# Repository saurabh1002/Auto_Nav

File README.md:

[Youtube video of 2D mapping in CoE, VJTI](https://youtu.be/3e1LqkSlBaA)

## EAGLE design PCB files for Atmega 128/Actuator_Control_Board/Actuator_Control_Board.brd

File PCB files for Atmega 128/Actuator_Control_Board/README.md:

This PCB splits the motor control signals from the microcontroller to each individual motor driver. It also provides an electrical braking circuit for the motors based on 5 Volt relays.

It also divides the incoming power from the batteries to each actuator.

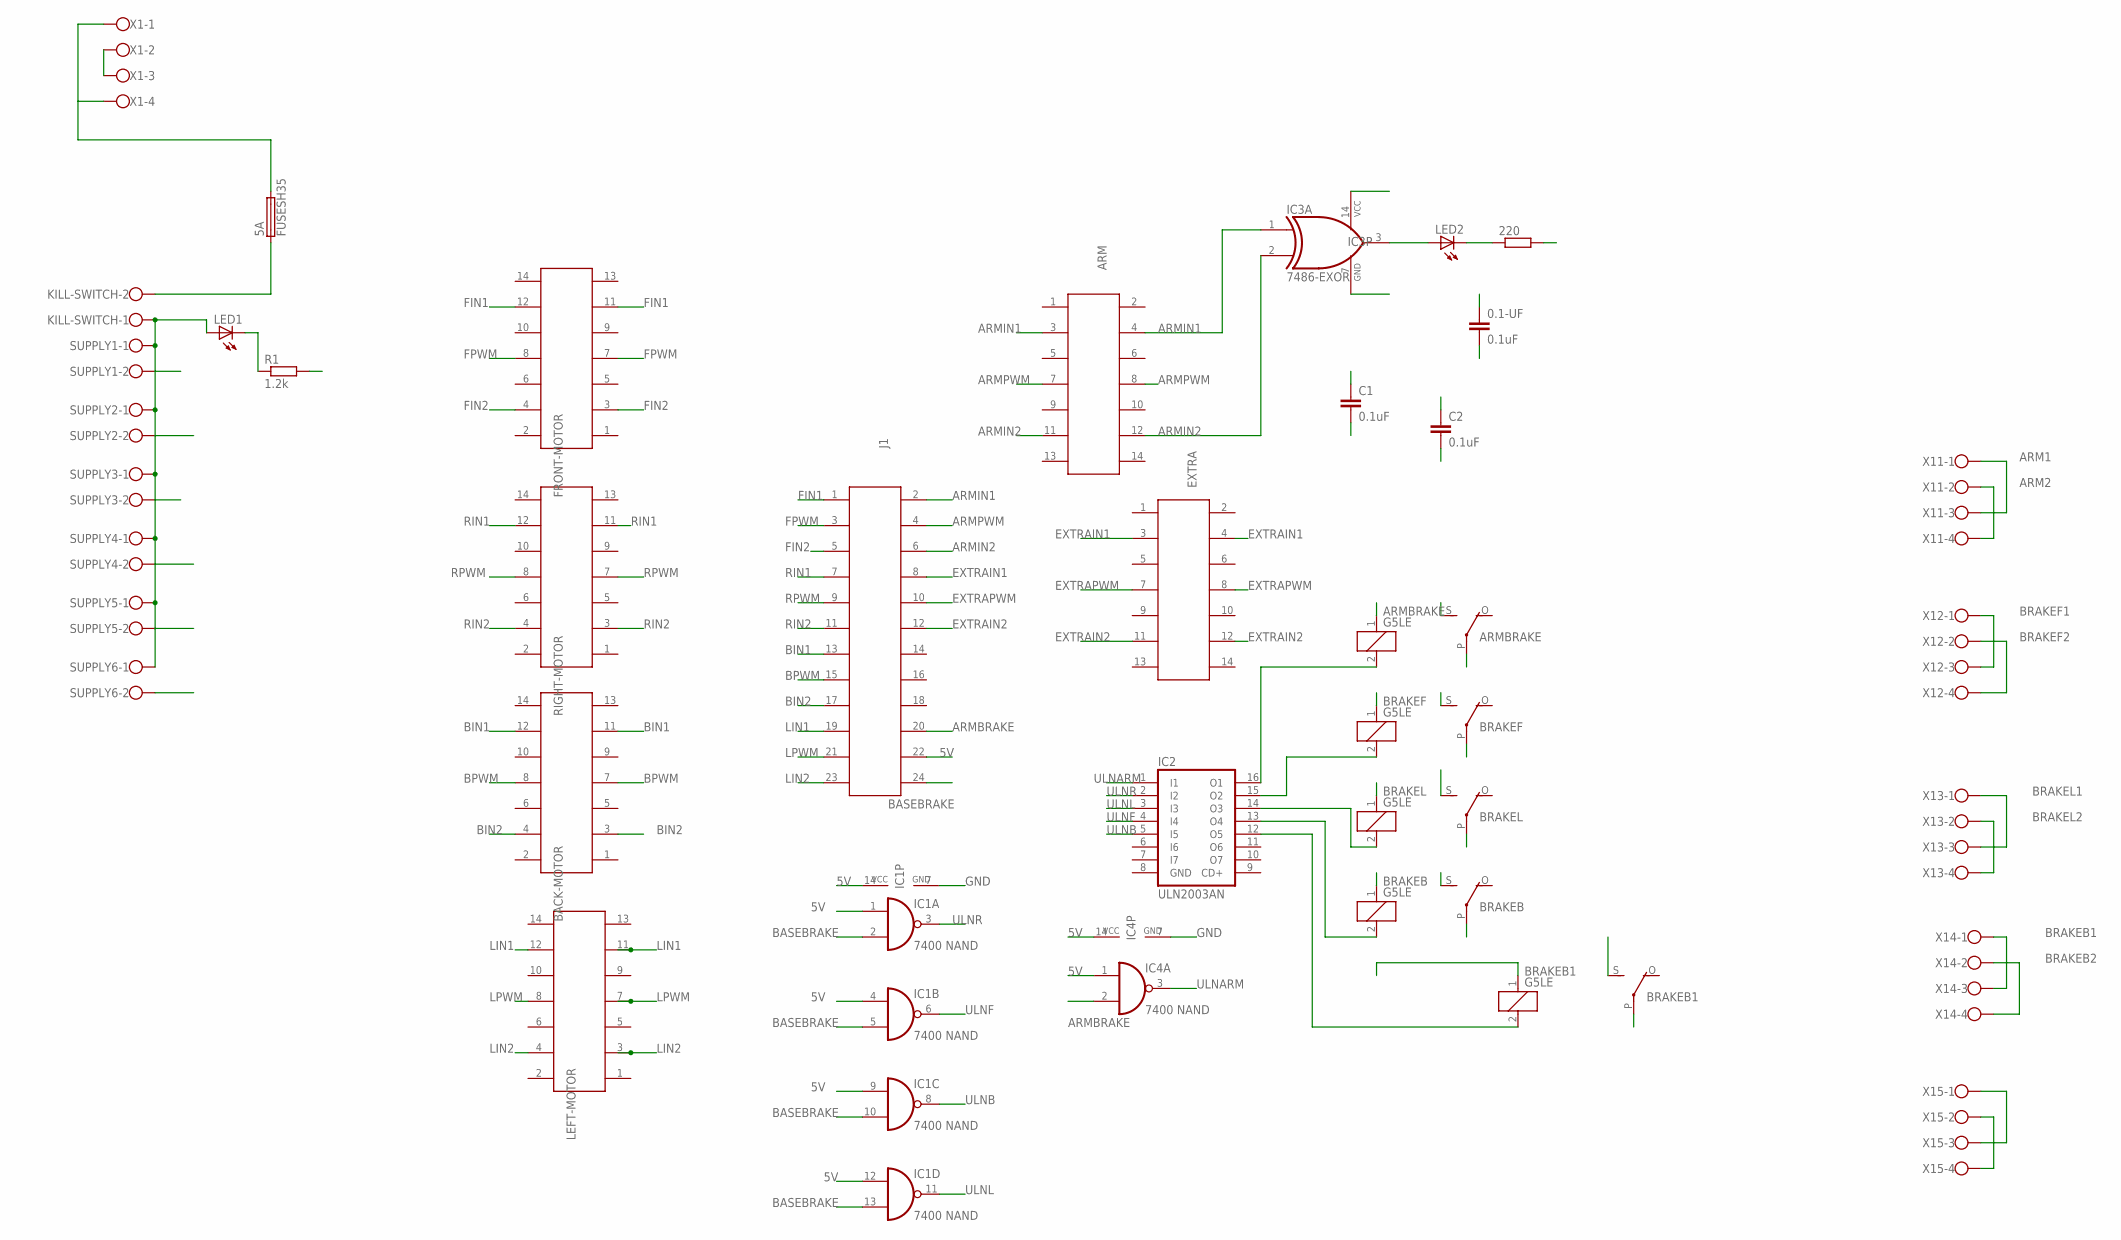
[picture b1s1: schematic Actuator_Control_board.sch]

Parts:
0.1-UF: 0.1uF; C5B2.5
5A: FUSESH35; SH25
220: R-EU_0207/10; 0207/10
ARM: 61201421621
ARMBRAKE: G5LE
BACK-MOTOR: 61201421621
BRAKEB, BRAKEB1: G5LE
BRAKEF: G5LE
BRAKEL: G5LE
C1, C2: 0.1uF; C5B2.5
EXTRA: 61201421621
FRONT-MOTOR: 61201421621
IC1, IC4: 7400 NAND; DIL14
IC2: ULN2003AN; DIL16
IC3: 7486-EXOR; DIL14
J1: 61202421621
KILL-SWITCH: W237-102
LED1, LED2: LED5MM
LEFT-MOTOR: 61201421621
R1: 1.2k; 0617/17
RIGHT-MOTOR: 61201421621
SUPPLY1, SUPPLY2, SUPPLY3, SUPPLY4, SUPPLY5, SUPPLY6: W237-102
X1, X11, X12, X13, X14, X15: W237-4

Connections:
5V: 0.1-UF.1, ARMBRAKE.1, BRAKEB.1, BRAKEB1.1, BRAKEF.1, BRAKEL.1, C1.1, C2.1, IC1.1 (I0), IC1.4 (I0), IC1.9 (I0), IC1.12 (I0), IC1.14 (VCC), IC3.14 (VCC), IC4.1 (I0), IC4.14 (VCC), J1.22
ARM1: ARMBRAKE.P, X11.1, X11.3
ARM2: ARMBRAKE.S, X11.2, X11.4
ARMBRAKE: IC4.2 (I1), J1.20
ARMIN1: ARM.3, ARM.4, IC3.1 (I0), J1.2
ARMIN2: ARM.11, ARM.12, IC3.2 (I1), J1.6
ARMPWM: ARM.7, ARM.8, J1.4
BASEBRAKE: IC1.2 (I1), IC1.5 (I1), IC1.10 (I1), IC1.13 (I1), J1.24
BIN1: BACK-MOTOR.11, BACK-MOTOR.12, J1.13
BIN2: BACK-MOTOR.3, BACK-MOTOR.4, J1.17
BPWM: BACK-MOTOR.7, BACK-MOTOR.8, J1.15
BRAKEB1: BRAKEB.P, X14.1, X14.3
BRAKEB2: BRAKEB.S, X14.2, X14.4
BRAKEF1: BRAKEF.P, X12.1, X12.3
BRAKEF2: BRAKEF.S, X12.2, X12.4
BRAKEL1: BRAKEL.P, X13.1, X13.3
BRAKEL2: BRAKEL.S, X13.2, X13.4
BRAKER1: BRAKEB1.P, X15.1, X15.3
BRAKER2: BRAKEB1.S, X15.2, X15.4
EXTRAIN1: EXTRA.3, EXTRA.4, J1.8
EXTRAIN2: EXTRA.11, EXTRA.12, J1.12
EXTRAPWM: EXTRA.7, EXTRA.8, J1.10
FIN1: FRONT-MOTOR.11, FRONT-MOTOR.12, J1.1
FIN2: FRONT-MOTOR.3, FRONT-MOTOR.4, J1.5
FPWM: FRONT-MOTOR.7, FRONT-MOTOR.8, J1.3
GND: 0.1-UF.2, 220.2, C1.2, C2.2, IC1.7 (GND), IC2.8 (GND), IC3.7 (GND), IC4.7 (GND), R1.2, SUPPLY1.2, SUPPLY2.2, SUPPLY3.2, SUPPLY4.2, SUPPLY5.2, SUPPLY6.2, X1.2, X1.3
LIN1: J1.19, LEFT-MOTOR.11, LEFT-MOTOR.12
LIN2: J1.23, LEFT-MOTOR.3, LEFT-MOTOR.4
LPWM: J1.21, LEFT-MOTOR.7, LEFT-MOTOR.8
unnamed: ARMBRAKE.2, IC2.16 (O1)
unnamed: BRAKEF.2, IC2.15 (O2)
unnamed: BRAKEL.2, IC2.14 (O3)
unnamed: BRAKEB.2, IC2.13 (O4)
unnamed: BRAKEB1.2, IC2.12 (O5)
unnamed: 5A.2, X1.1, X1.4
unnamed: 5A.1, KILL-SWITCH.2
unnamed: KILL-SWITCH.1, LED1.A, SUPPLY1.1, SUPPLY2.1, SUPPLY3.1, SUPPLY4.1, SUPPLY5.1, SUPPLY6.1
unnamed: LED1.K (C), R1.1
unnamed: IC3.3 (O), LED2.A
unnamed: 220.1, LED2.K (C)
RIN1: J1.7, RIGHT-MOTOR.11, RIGHT-MOTOR.12
RIN2: J1.11, RIGHT-MOTOR.3, RIGHT-MOTOR.4
RPWM: J1.9, RIGHT-MOTOR.7, RIGHT-MOTOR.8
ULNARM: IC2.1 (I1), IC4.3 (O)
ULNB: IC1.8 (O), IC2.5 (I5)
ULNF: IC1.6 (O), IC2.4 (I4)
ULNL: IC1.11 (O), IC2.3 (I3)
ULNR: IC1.3 (O), IC2.2 (I2)

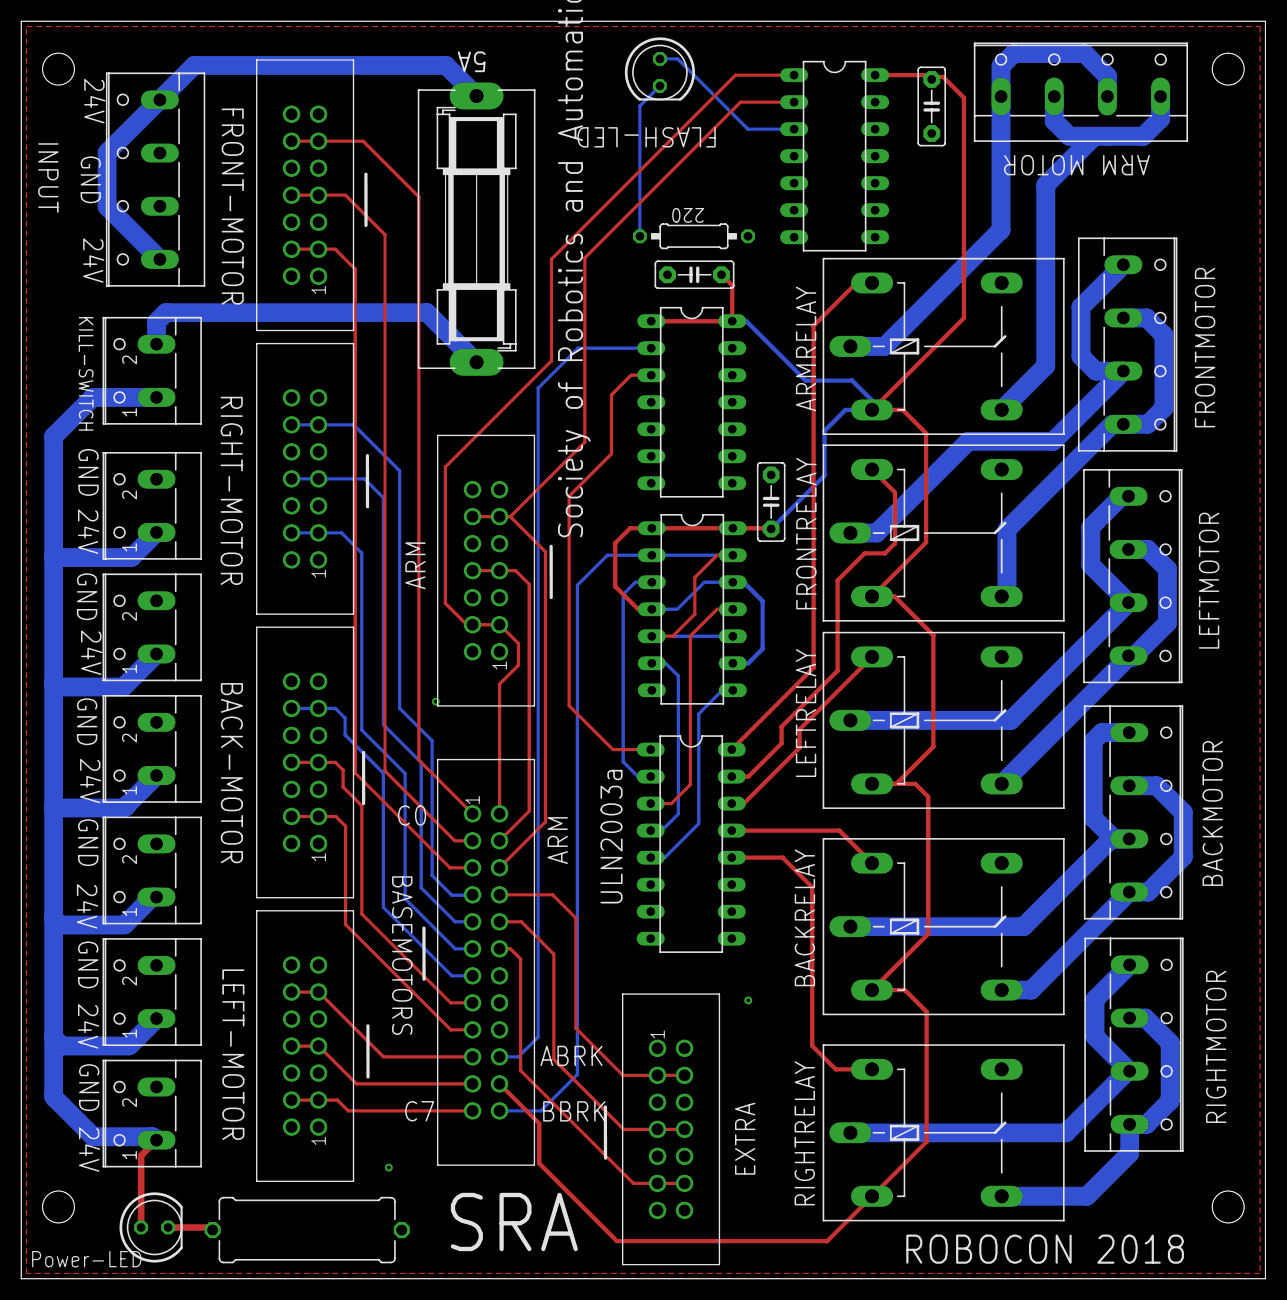
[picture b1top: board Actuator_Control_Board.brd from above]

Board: 2 copper layers, 117.0 x 118.2 mm, 37 parts (0 on the bottom side), 48 nets.

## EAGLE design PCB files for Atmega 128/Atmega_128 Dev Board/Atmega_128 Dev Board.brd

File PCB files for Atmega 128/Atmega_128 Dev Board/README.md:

This is the main PCB for the Atmega 128 based development board. The Atmega 128 breakout board must be inserted into this PCB and a 12x2 FRC cable must be connected to the Actuator control board for transmitting IO signals to the motor drivers.

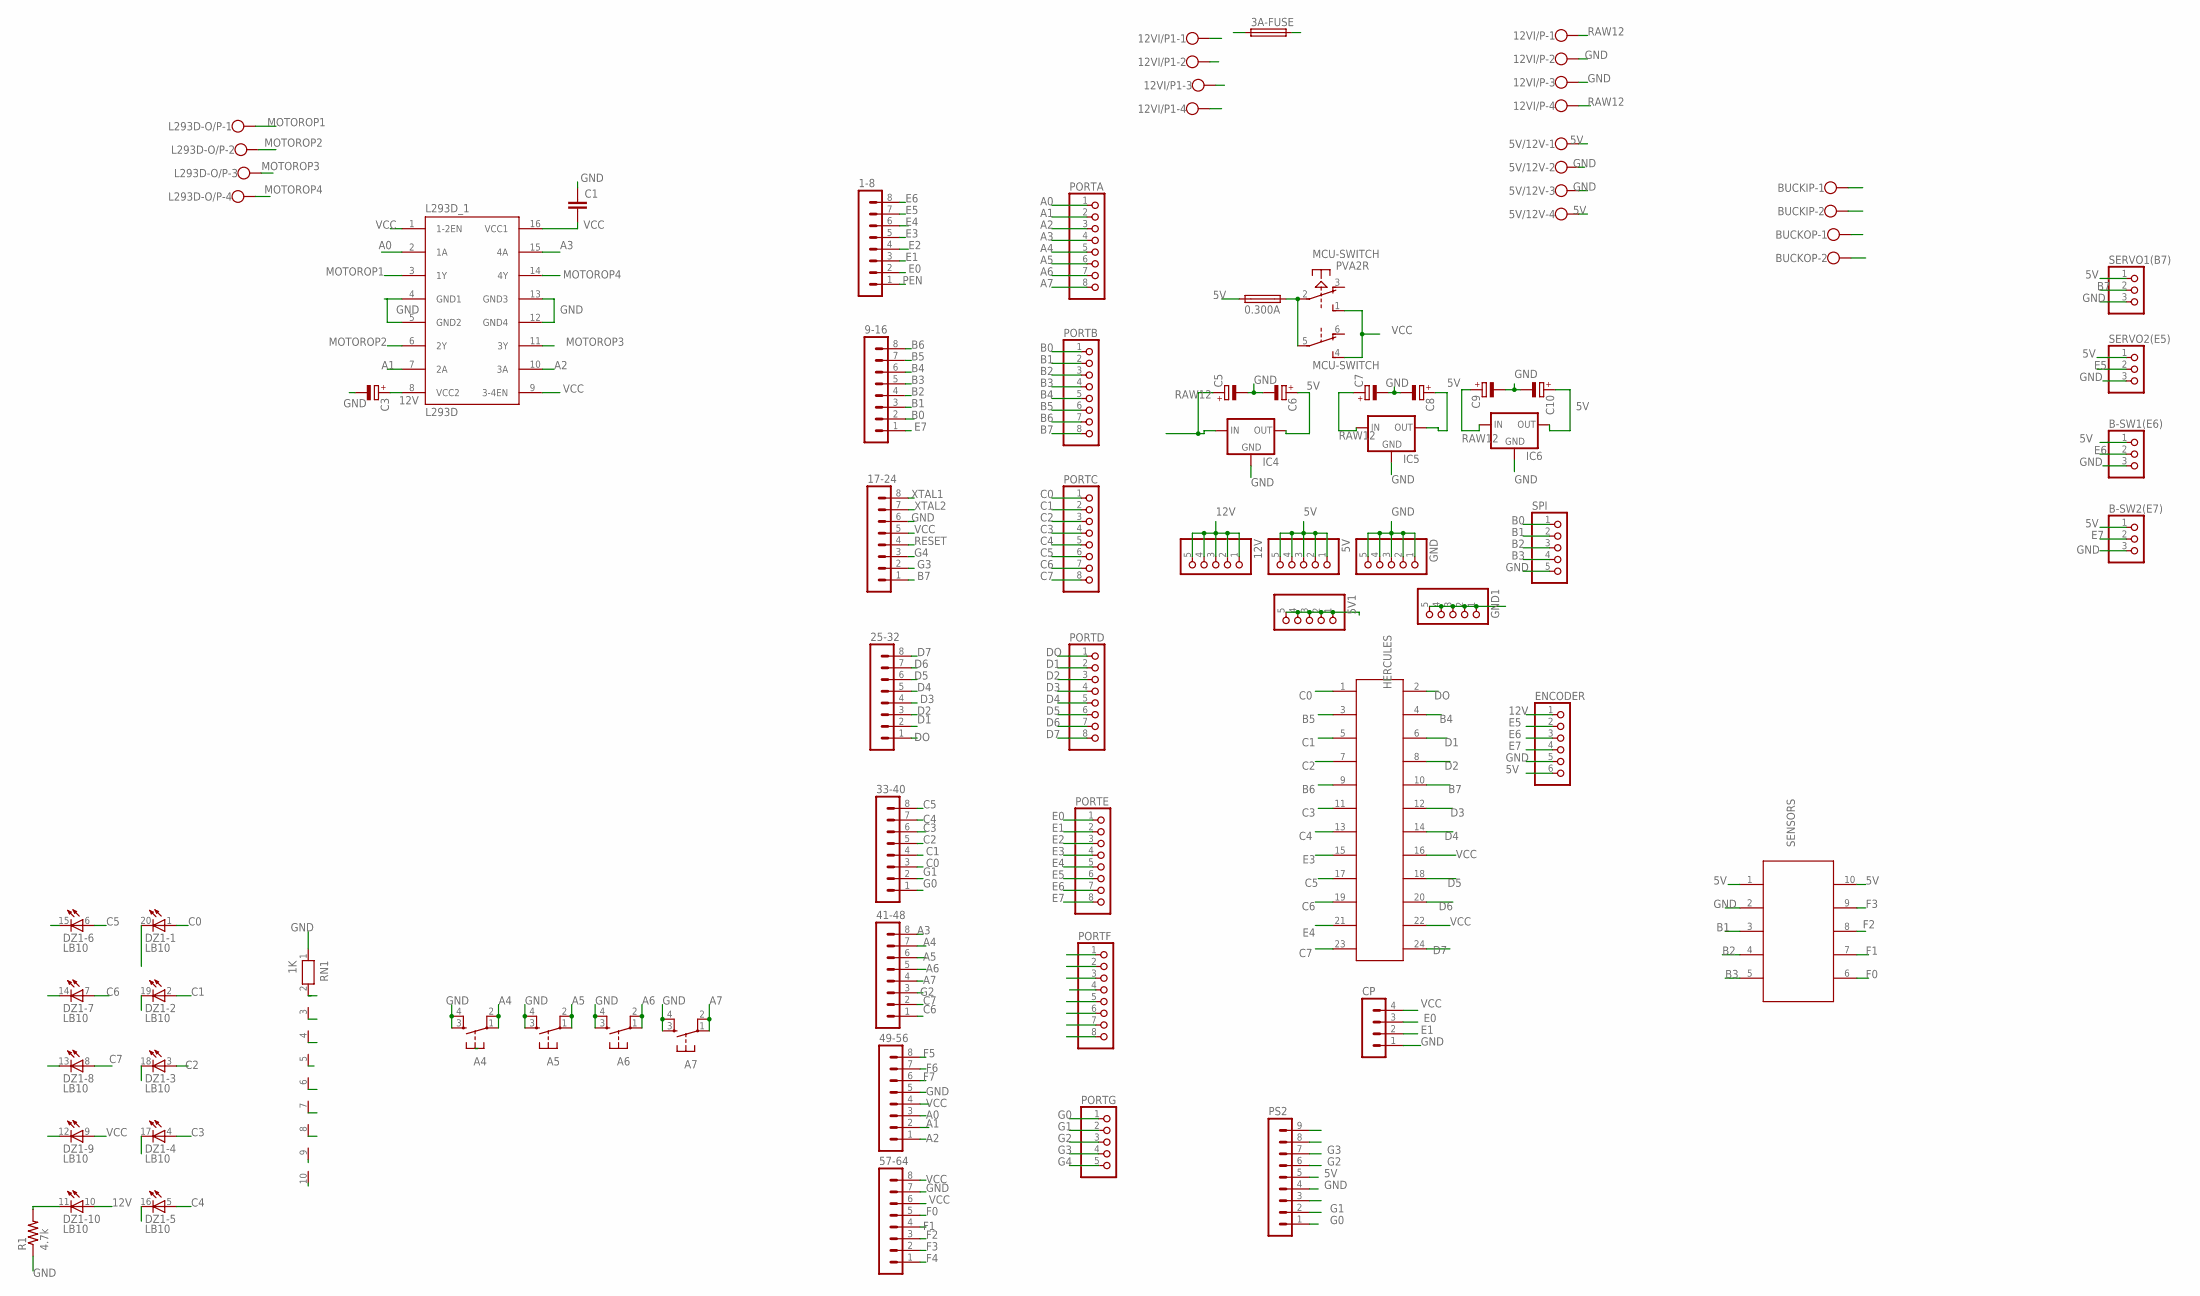
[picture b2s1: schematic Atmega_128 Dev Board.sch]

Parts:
0.300A, 3A-FUSE: SH25
1-8, 9-16, 17-24, 25-32, 33-40, 41-48, 49-56, 57-64: MA08-1
5V, 5V1, 12V: PINHD-1X5; 1X05
5V/12V, 12VI/P, 12VI/P1: W237-4
A4, A5, A6, A7: DTS-6
B-SW1(E6), B-SW2(E7): PINHD-1X3; 1X03
BUCKIP: W237-102
BUCKOP: W237-102
C1: C5/2.5; C5B2.5
C3, C5, C6, C7, C8, C9, C10: CPOL-EUE2.5-5; E2,5-5
CP: MA04-1
DZ1: LB10
ENCODER: PINHD-1X6; 1X06
GND, GND1: PINHD-1X5; 1X05
HERCULES: 61202421621
IC4, IC5, IC6: 78XXS
L293D-O/P: W237-4
L293D_1: L293D; DIL16
MCU-SWITCH: PVA2R
PORTA: PINHD-1X8; 1X08
PORTB: PINHD-1X8; 1X08
PORTC: PINHD-1X8; 1X08
PORTD: PINHD-1X8; 1X08
PORTE: PINHD-1X8; 1X08
PORTF: PINHD-1X8; 1X08
PORTG: PINHD-1X5; 1X05
PS2: MA09-1
R1: 4.7k; 0204/7
RN1: 1K; RN-10
SENSORS: 66101021622
SERVO1(B7), SERVO2(E5): PINHD-1X3; 1X03
SPI: PINHD-1X5; 1X05

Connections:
2: DZ1.12 (C), RN1.2
3: DZ1.13 (C), RN1.3
4: DZ1.14 (C), RN1.4
5: DZ1.15 (C), RN1.5
5V: 0.300A.2, 5V.1, 5V.2, 5V.3, 5V.4, 5V.5, 5V1.1, 5V1.2, 5V1.3, 5V1.4, 5V1.5, 5V/12V.1, 5V/12V.4, B-SW1(E6).1, B-SW2(E7).1, BUCKOP.2, C6.+, C8.+, C10.+, ENCODER.6, IC4.OUT, IC5.OUT, IC6.OUT, PS2.5, SENSORS.1 (6), SENSORS.10 (1), SERVO1(B7).1, SERVO2(E5).1
5V-F: 0.300A.1, MCU-SWITCH.2, MCU-SWITCH.5
6: DZ1.16 (C), RN1.6
7: DZ1.17 (C), RN1.7
8: DZ1.18 (C), RN1.8
9: DZ1.19 (C), RN1.9
10: DZ1.20 (C), RN1.10
12V: 3A-FUSE.2, 12V.1, 12V.2, 12V.3, 12V.4, 12V.5, C3.+, DZ1.10 (A), ENCODER.1, L293D_1.8 (VCC2)
A0: 49-56.3, L293D_1.2 (1A), PORTA.1
A1: 49-56.2, L293D_1.7 (2A), PORTA.2
A2: 49-56.1, L293D_1.10 (3A), PORTA.3
A3: 41-48.8, L293D_1.15 (4A), PORTA.4
A4: 41-48.7, A4.1, A4.2, PORTA.5
A5: 41-48.6, A5.1, A5.2, PORTA.6
A6: 41-48.5, A6.1, A6.2, PORTA.7
A7: 41-48.4, A7.1, A7.2, PORTA.8
B0: 9-16.2, PORTB.1, SPI.1
B1: 9-16.3, PORTB.2, SENSORS.3 (8), SPI.2
B2: 9-16.4, PORTB.3, SENSORS.4 (9), SPI.3
B3: 9-16.5, PORTB.4, SENSORS.5 (10), SPI.4
B4: 9-16.6, HERCULES.4, PORTB.5
B5: 9-16.7, HERCULES.3, PORTB.6
B6: 9-16.8, HERCULES.9, PORTB.7
B7: 17-24.1, HERCULES.10, PORTB.8, SERVO1(B7).2
C0: 33-40.3, DZ1.1 (A), HERCULES.1, PORTC.1
C1: 33-40.4, DZ1.2 (A), HERCULES.5, PORTC.2
C2: 33-40.5, DZ1.3 (A), HERCULES.7, PORTC.3
C3: 33-40.6, DZ1.4 (A), HERCULES.11, PORTC.4
C4: 33-40.7, DZ1.5 (A), HERCULES.13, PORTC.5
C5: 33-40.8, DZ1.6 (A), HERCULES.17, PORTC.6
C6: 41-48.1, DZ1.7 (A), HERCULES.19, PORTC.7
C7: 41-48.2, DZ1.8 (A), HERCULES.23, PORTC.8
D1: 25-32.2, HERCULES.6, PORTD.2
D2: 25-32.3, HERCULES.8, PORTD.3
D3: 25-32.4, HERCULES.12, PORTD.4
D4: 25-32.5, HERCULES.14, PORTD.5
D5: 25-32.6, HERCULES.18, PORTD.6
D6: 25-32.7, HERCULES.20, PORTD.7
D7: 25-32.8, HERCULES.24, PORTD.8
DO: 25-32.1, HERCULES.2, PORTD.1
E0: 1-8.2, CP.3, PORTE.1
E1: 1-8.3, CP.2, PORTE.2
E2: 1-8.4, PORTE.3
E3: 1-8.5, HERCULES.15, PORTE.4
E4: 1-8.6, HERCULES.21, PORTE.5
E5: 1-8.7, ENCODER.2, PORTE.6, SERVO2(E5).2
E6: 1-8.8, B-SW1(E6).2, ENCODER.3, PORTE.7
E7: 9-16.1, B-SW2(E7).2, ENCODER.4, PORTE.8
F0: 57-64.5, PORTF.1, SENSORS.6 (5)
F1: 57-64.4, PORTF.2, SENSORS.7 (4)
F2: 57-64.3, PORTF.3, SENSORS.8 (3)
F3: 57-64.2, PORTF.4, SENSORS.9 (2)
F4: 57-64.1, PORTF.5
F5: 49-56.8, PORTF.6
F6: 49-56.7, PORTF.7
F7: 49-56.6, PORTF.8
G0: 33-40.1, PORTG.1, PS2.1
G1: 33-40.2, PORTG.2, PS2.2
G2: 41-48.3, PORTG.3, PS2.6
G3: 17-24.2, PORTG.4, PS2.7
G4: 17-24.3, PORTG.5
GND: 5V/12V.2, 5V/12V.3, 12VI/P.2, 12VI/P.3, 12VI/P1.2, 12VI/P1.3, 17-24.6, 49-56.5, 57-64.7, A4.3, A4.4, A5.3, A5.4, A6.3, A6.4, A7.3, A7.4, B-SW1(E6).3, B-SW2(E7).3, BUCKIP.2, BUCKOP.1, C1.1, C3.-, C5.-, C6.-, C7.-, C8.-, C9.-, C10.-, CP.1, ENCODER.5, GND.1, GND.2, GND.3, GND.4, GND.5, GND1.1, GND1.2, GND1.3, GND1.4, GND1.5, IC4.GND, IC5.GND, IC6.GND, L293D_1.4 (GND1), L293D_1.5 (GND2), L293D_1.12 (GND4), L293D_1.13 (GND3), PS2.4, R1.1, RN1.1, SENSORS.2 (7), SERVO1(B7).3, SERVO2(E5).3, SPI.5
MOTOROP1: L293D-O/P.1, L293D_1.3 (1Y)
MOTOROP2: L293D-O/P.2, L293D_1.6 (2Y)
MOTOROP3: L293D-O/P.3, L293D_1.11 (3Y)
MOTOROP4: L293D-O/P.4, L293D_1.14 (4Y)
unnamed: DZ1.11 (C), R1.2
PEN: 1-8.1
RAW12: 3A-FUSE.1, 12VI/P.1, 12VI/P.4, 12VI/P1.1, 12VI/P1.4, BUCKIP.1, C5.+, C7.+, C9.+, IC4.IN, IC5.IN, IC6.IN
RESET: 17-24.4
VCC: 17-24.5, 49-56.4, 57-64.6, 57-64.8, C1.2, CP.4, DZ1.9 (A), HERCULES.16, HERCULES.22, L293D_1.1 (1-2EN), L293D_1.9 (3-4EN), L293D_1.16 (VCC1), MCU-SWITCH.1 (S), MCU-SWITCH.4 (S)
XTAL1: 17-24.8
XTAL2: 17-24.7

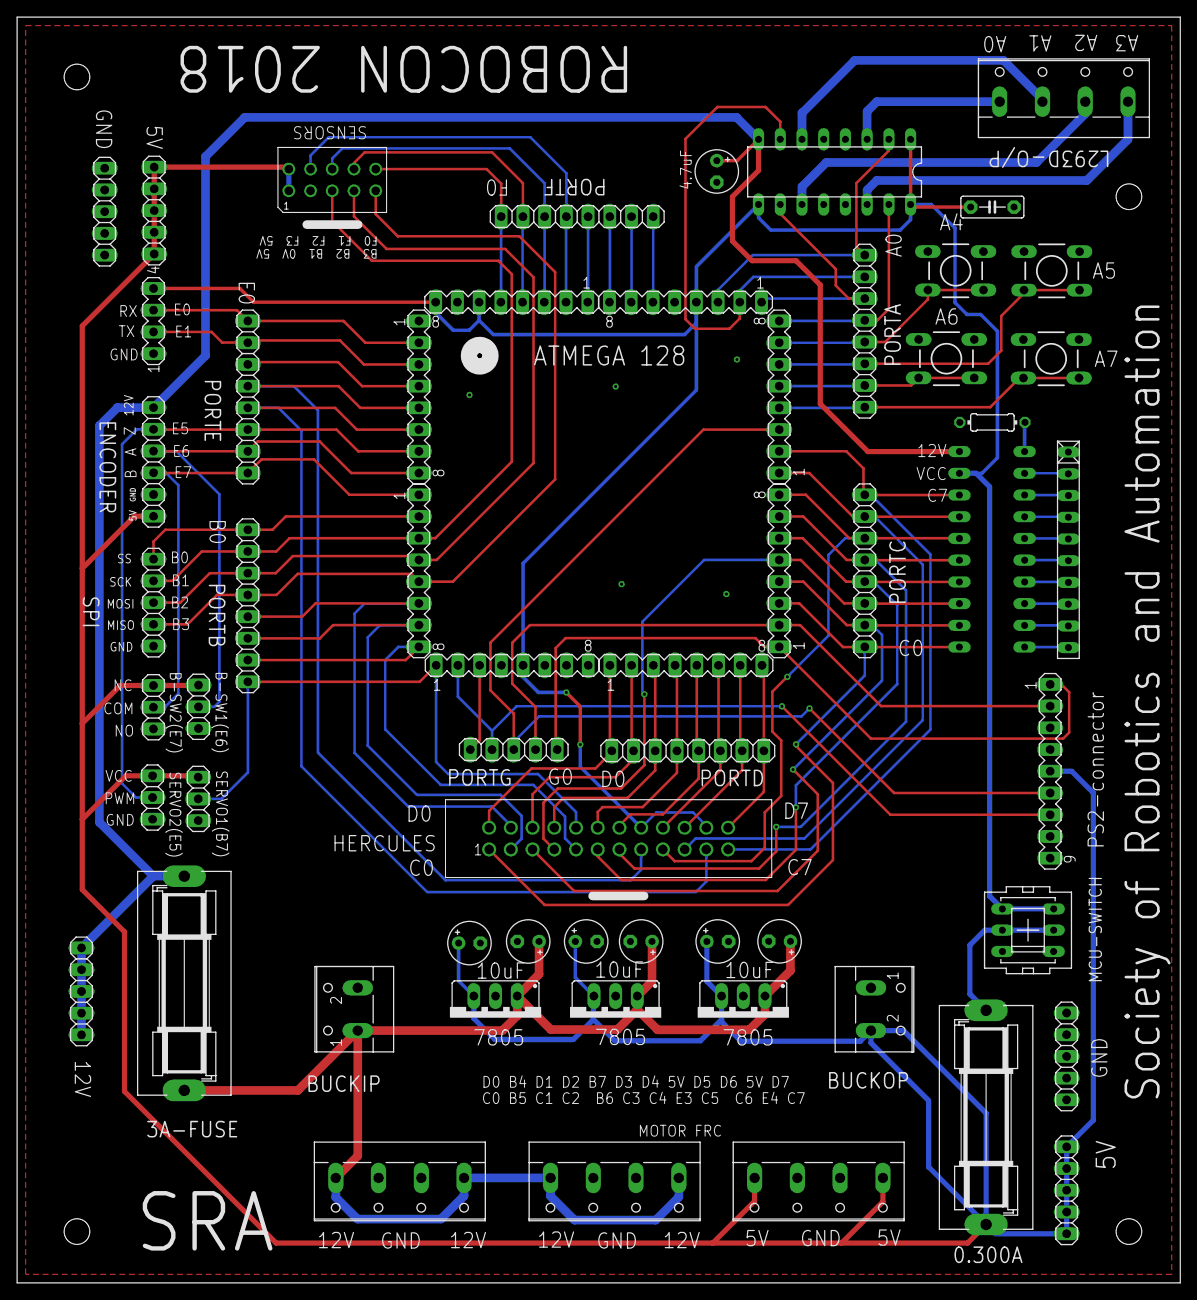
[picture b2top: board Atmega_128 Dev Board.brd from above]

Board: 2 copper layers, 136.0 x 148.0 mm, 58 parts (1 on the bottom side), 73 nets.

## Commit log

2019-01-16 Initial commit
    Package for mapping, localisation and autonomous navigation.
2019-01-17 Added the schematic files for the PCBs used in this project
2019-01-17 Changes in file path
2019-10-12 Add README.md
2020-02-05 Add license

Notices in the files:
parts and their libraries:
Wurth_Elektronik_Electromechanic_Wire_to: Copyright: Würth Elektronik
